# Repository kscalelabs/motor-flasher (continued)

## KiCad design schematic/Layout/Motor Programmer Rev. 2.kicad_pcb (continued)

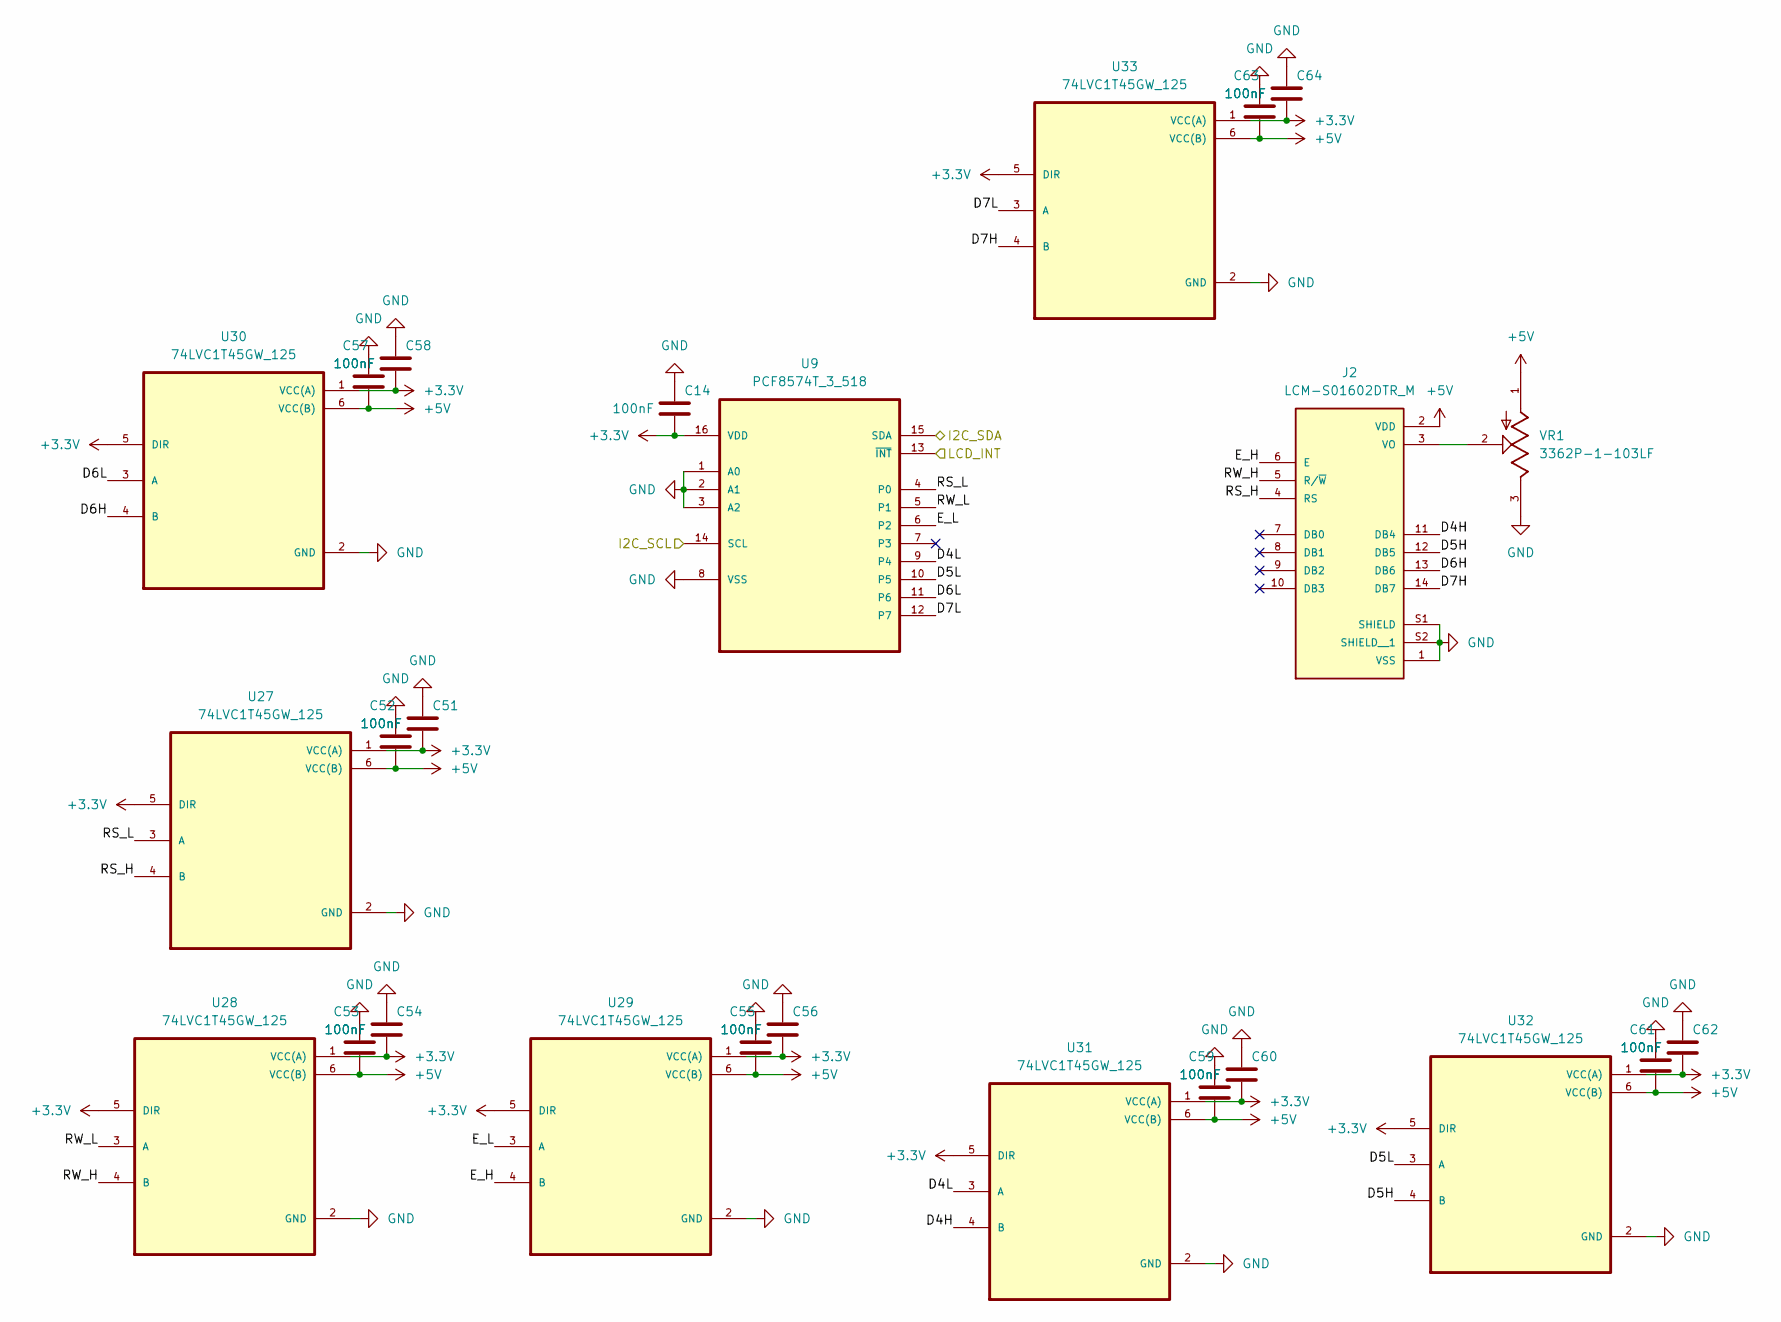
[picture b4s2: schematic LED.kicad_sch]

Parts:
C14, C51, C52, C53, C54, C55, C56, C57, C58, C59, C60, C61, C62, C63, C64: 100nF; C_0402_1005Metric
J2: LCM-S01602DTR_M; LCD_LCM-S01602DTR_M; PARTREV 9/11/02
U9: PCF8574T_3_518; SOIC127P1032X265-16N; MPN PCF8574T/3,518
U27, U28, U29, U30, U31, U32, U33: 74LVC1T45GW_125; SOP65P210X110-6N
VR1: 3362P-1-103LF; TRIM_3362P-1-103LF; PARTREV 08/26/10

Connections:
+3.3V: C14.2, C51.2, C54.2, C56.2, C58.2, C60.2, C62.2, C64.2, U9.16 (VDD), U27.1 (VCC(A)), U27.5 (DIR), U28.1 (VCC(A)), U28.5 (DIR), U29.1 (VCC(A)), U29.5 (DIR), U30.1 (VCC(A)), U30.5 (DIR), U31.1 (VCC(A)), U31.5 (DIR), U32.1 (VCC(A)), U32.5 (DIR), U33.1 (VCC(A)), U33.5 (DIR); also elsewhere on the board
+5V: C52.2, C53.2, C55.2, C57.2, C59.2, C61.2, C63.2, J2.2 (VDD), U27.6 (VCC(B)), U28.6 (VCC(B)), U29.6 (VCC(B)), U30.6 (VCC(B)), U31.6 (VCC(B)), U32.6 (VCC(B)), U33.6 (VCC(B)), VR1.1; also elsewhere on the board
/LCD_Int: U9.13 (~INT); also elsewhere on the board
/LED/D4H: J2.11 (DB4), U31.4 (B)
/LED/D4L: U9.9 (P4), U31.3 (A)
/LED/D5H: J2.12 (DB5), U32.4 (B)
/LED/D5L: U9.10 (P5), U32.3 (A)
/LED/D6H: J2.13 (DB6), U30.4 (B)
/LED/D6L: U9.11 (P6), U30.3 (A)
/LED/D7H: J2.14 (DB7), U33.4 (B)
/LED/D7L: U9.12 (P7), U33.3 (A)
/LED/E_H: J2.6 (E), U29.4 (B)
/LED/E_L: U9.6 (P2), U29.3 (A)
/LED/RS_H: J2.4 (RS), U27.4 (B)
/LED/RS_L: U9.4 (P0), U27.3 (A)
/LED/RW_H: J2.5 (R/~W), U28.4 (B)
/LED/RW_L: U9.5 (P1), U28.3 (A)
/SCL: U9.14 (SCL); also elsewhere on the board
/SDA: U9.15 (SDA); also elsewhere on the board
GND: C14.1, C51.1, C52.1, C53.1, C54.1, C55.1, C56.1, C57.1, C58.1, C59.1, C60.1, C61.1, C62.1, C63.1, C64.1, J2.1 (VSS), J2.S1 (SHIELD), J2.S2 (SHIELD__1), U9.1 (A0), U9.2 (A1), U9.3 (A2), U9.8 (VSS), U27.2 (GND), U28.2 (GND), U29.2 (GND), U30.2 (GND), U31.2 (GND), U32.2 (GND), U33.2 (GND), VR1.3; also elsewhere on the board
unnamed: J2.3 (VO), VR1.2

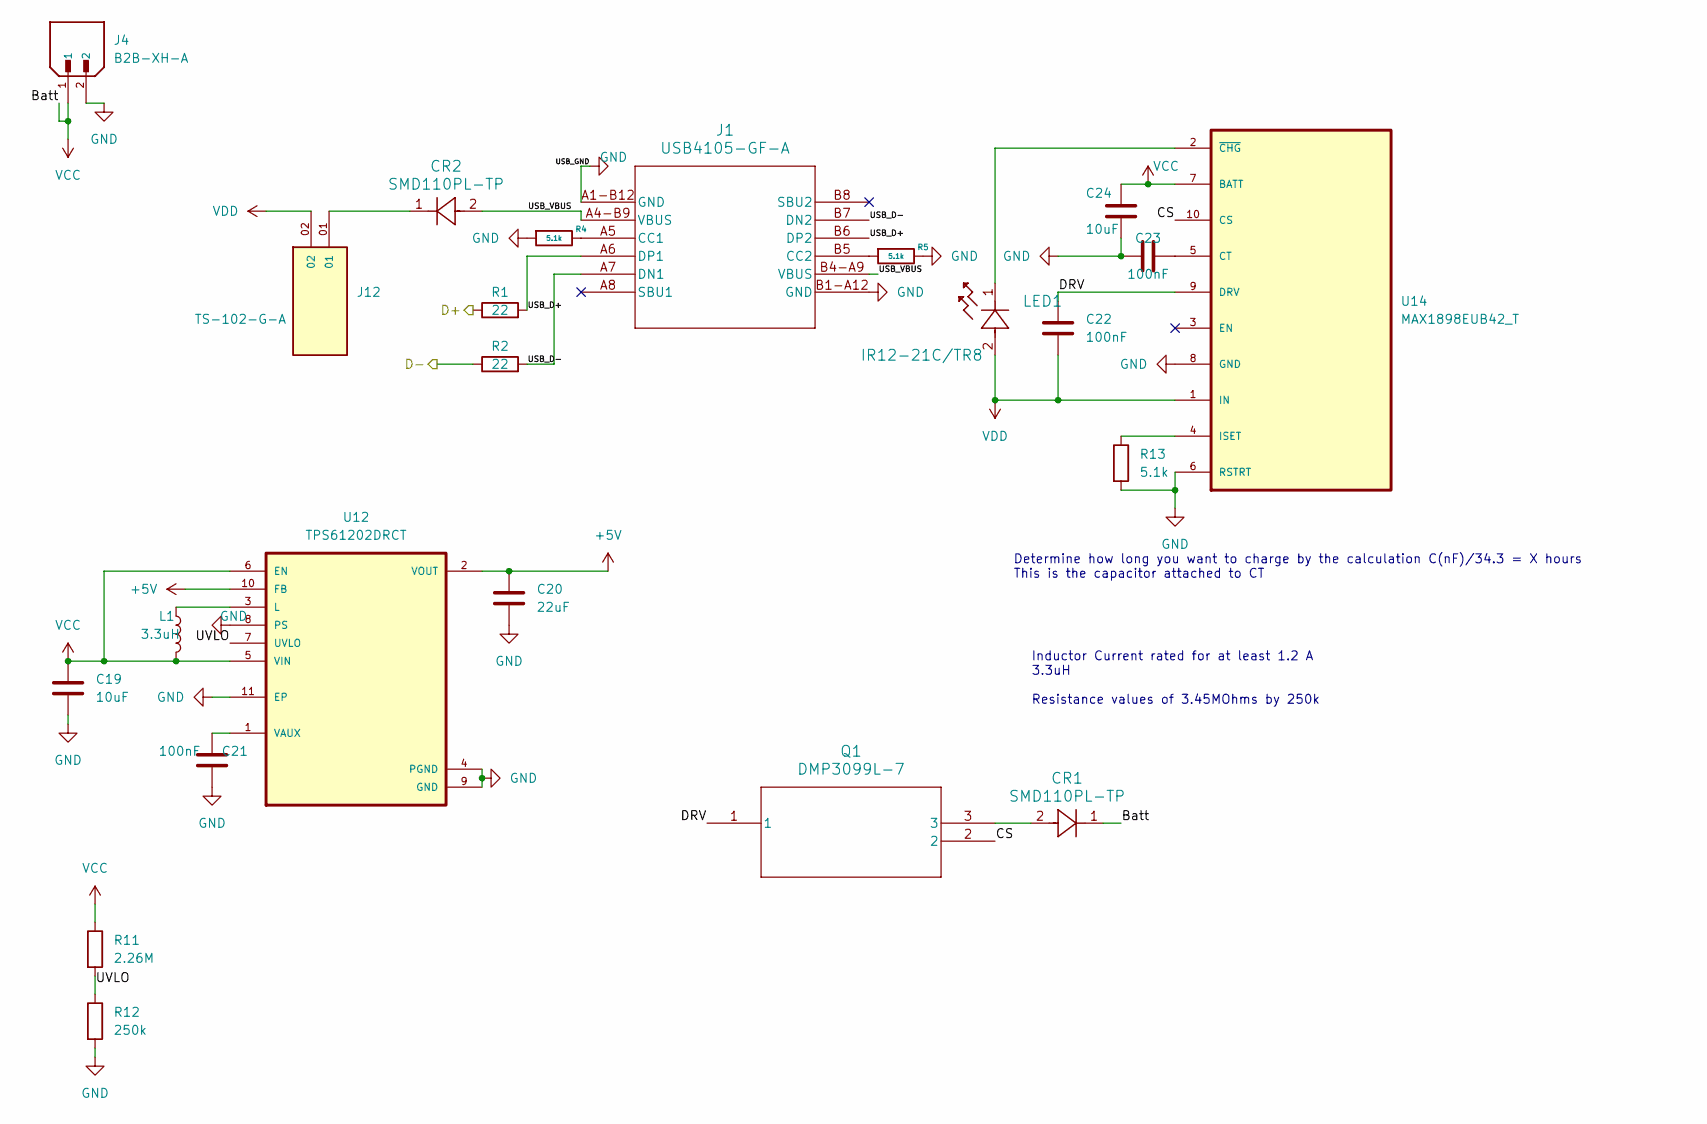
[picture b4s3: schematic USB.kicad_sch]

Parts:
C19, C24: 10uF; C_0805_2012Metric
C20: 22uF; C_0603_1608Metric
C21, C22, C23: 100nF; C_0402_1005Metric
CR1, CR2: SMD110PL-TP; SOD-123FL_MCC
J1: USB4105-GF-A; GCT_USB4105-GF-A
J4: B2B-XH-A; JST_B2B-XH-A; PARTREV N/A
J12: TS-102-G-A; SAMTEC_TS-102-G-A; PARTREV R
L1: 3.3uH; IND_TAIYO_NRS4018_TAY
LED1: IR12-21C/TR8; LED_IR12-21C&slash_TR8_EVE
Q1: DMP3099L-7; DMP3099L-7_DIO
R1, R2: 22; R_0402_1005Metric
R4, R5, R13: 5.1k; R_0603_1608Metric
R11: 2.26M; R_0603_1608Metric
R12: 250k; R_0805_2012Metric
U12: TPS61202DRCT; VREG_V62_16624-01YE
U14: MAX1898EUB42_T; SOP50P490X110-10N

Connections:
+5V: C20.1, U12.2 (VOUT), U12.10 (FB); also elsewhere on the board
/D+: R1.1; also elsewhere on the board
/D-: R2.1; also elsewhere on the board
/USB + Power Source/CS: Q1.2, U14.10 (CS)
/USB + Power Source/DRV: C22.2, Q1.1, U14.9 (DRV)
/USB + Power Source/USB_D+: J1.A6 (DP1), J1.B6 (DP2), R1.2
/USB + Power Source/USB_D-: J1.A7 (DN1), J1.B7 (DN2), R2.2
/USB + Power Source/USB_VBUS: CR2.2, J1.A4-B9 (VBUS), J1.B4-A9 (VBUS)
/USB + Power Source/UVLO: R11.2, R12.1, U12.7 (UVLO)
GND: C19.2, C20.2, C21.2, C23.2, C24.2, J1.A1-B12 (GND), J1.B1-A12 (GND), J4.2, R4.2, R5.1, R12.2, R13.2, U12.4 (PGND), U12.8 (PS), U12.9 (GND), U12.11 (EP), U14.6 (RSTRT), U14.8 (GND); also elsewhere on the board
unnamed: CR1.2, Q1.3
unnamed: CR2.1, J12.01
unnamed: J1.A5 (CC1), R4.1
unnamed: J1.B5 (CC2), R5.2
unnamed: L1.1, U12.3 (L)
unnamed: C21.1, U12.1 (VAUX)
unnamed: C23.1, U14.5 (CT)
unnamed: R13.1, U14.4 (ISET)
unnamed: LED1.1, U14.2 (~CHG)
VCC: C19.1, C24.1, CR1.1, J4.1, L1.2, R11.1, U12.5 (VIN), U12.6 (EN), U14.7 (BATT); also elsewhere on the board
VDD: C22.1, J12.02, LED1.2, U14.1 (IN)

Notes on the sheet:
Inductor Current rated for at least 1.2 A 3.3uH Resistance values of 3.45MOhms by 250k
Determine how long you want to charge by the calculation C(nF)/34.3 = X hours This is the capacitor attached to CT

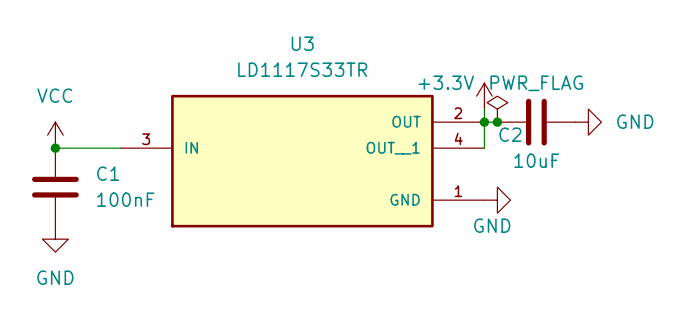
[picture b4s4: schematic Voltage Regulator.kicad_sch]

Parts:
C1: 100nF; C_0402_1005Metric
C2: 10uF; C_0805_2012Metric
U3: LD1117S33TR; SOT230P700X180-4N

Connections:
+3.3V: C2.2, U3.2 (OUT), U3.4 (OUT__1); also elsewhere on the board
GND: C1.2, C2.1, U3.1 (GND); also elsewhere on the board
VCC: C1.1, U3.3 (IN); also elsewhere on the board

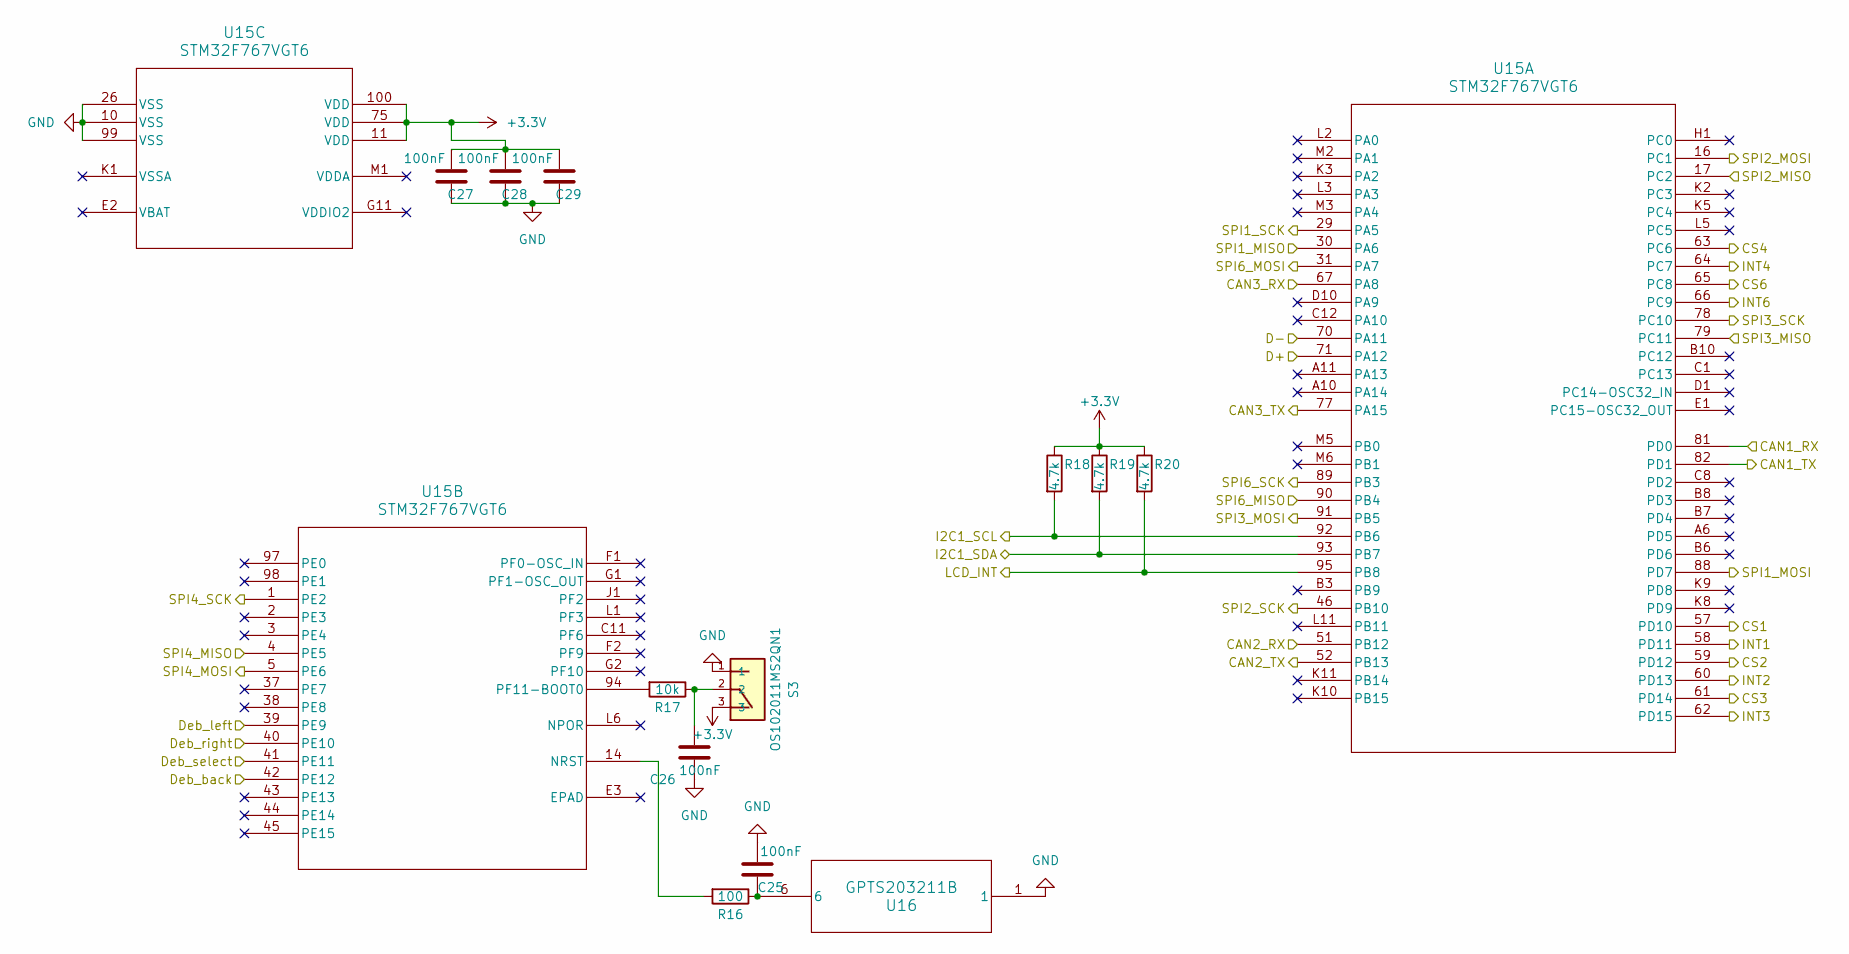
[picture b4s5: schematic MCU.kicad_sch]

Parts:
C25, C26, C27, C28, C29: 100nF; C_0402_1005Metric
R16: 100; R_0402_1005Metric
R17: 10k; R_0402_1005Metric
R18, R19, R20: 4.7k; R_0402_1005Metric
S3: OS102011MS2QN1; SW_OS102011MS2QN1
U15: STM32F767VGT6; QFP50P1600X1600X160-100N
U16: GPTS203211B; SWITCH_03211B

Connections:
+3.3V: C27.1, C28.1, C29.1, R18.1, R19.1, R20.1, S3.3, U15.11 (VDD), U15.75 (VDD), U15.100 (VDD); also elsewhere on the board
/CAN1_RX: U15.81 (PD0); also elsewhere on the board
/CAN1_TX: U15.82 (PD1); also elsewhere on the board
/CAN2_RX: U15.51 (PB12); also elsewhere on the board
/CAN2_TX: U15.52 (PB13); also elsewhere on the board
/CAN3_RX: U15.67 (PA8); also elsewhere on the board
/CAN3_TX: U15.77 (PA15); also elsewhere on the board
/CS1: U15.57 (PD10); also elsewhere on the board
/CS2: U15.59 (PD12); also elsewhere on the board
/CS3: U15.61 (PD14); also elsewhere on the board
/CS4: U15.63 (PC6); also elsewhere on the board
/CS6: U15.65 (PC8); also elsewhere on the board
/D+: U15.71 (PA12); also elsewhere on the board
/D-: U15.70 (PA11); also elsewhere on the board
/Deb_back: U15.42 (PE12); also elsewhere on the board
/Deb_left: U15.39 (PE9); also elsewhere on the board
/Deb_right: U15.40 (PE10); also elsewhere on the board
/Deb_select: U15.41 (PE11); also elsewhere on the board
/INT1: U15.58 (PD11); also elsewhere on the board
/INT2: U15.60 (PD13); also elsewhere on the board
/INT3: U15.62 (PD15); also elsewhere on the board
/INT4: U15.64 (PC7); also elsewhere on the board
/INT6: U15.66 (PC9); also elsewhere on the board
/LCD_Int: R20.2, U15.95 (PB8); also elsewhere on the board
/SCL: R18.2, U15.92 (PB6); also elsewhere on the board
/SDA: R19.2, U15.93 (PB7); also elsewhere on the board
/SPI1_MISO: U15.30 (PA6); also elsewhere on the board
/SPI1_MOSI: U15.88 (PD7); also elsewhere on the board
/SPI1_SCK: U15.29 (PA5); also elsewhere on the board
/SPI2_MISO: U15.17 (PC2); also elsewhere on the board
/SPI2_MOSI: U15.16 (PC1); also elsewhere on the board
/SPI2_SCK: U15.46 (PB10); also elsewhere on the board
/SPI3_MISO: U15.79 (PC11); also elsewhere on the board
/SPI3_MOSI: U15.91 (PB5); also elsewhere on the board
/SPI3_SCK: U15.78 (PC10); also elsewhere on the board
/SPI4_MISO: U15.4 (PE5); also elsewhere on the board
/SPI4_MOSI: U15.5 (PE6); also elsewhere on the board
/SPI4_SCK: U15.1 (PE2); also elsewhere on the board
/SPI6_MISO: U15.90 (PB4); also elsewhere on the board
/SPI6_MOSI: U15.31 (PA7); also elsewhere on the board
/SPI6_SCK: U15.89 (PB3); also elsewhere on the board
GND: C25.2, C26.1, C27.2, C28.2, C29.2, S3.1, U15.10 (VSS), U15.26 (VSS), U15.99 (VSS), U16.1; also elsewhere on the board
unnamed: C25.1, R16.1, U16.6
unnamed: C26.2, R17.1, S3.2
unnamed: R16.2, U15.14 (NRST)
unnamed: R17.2, U15.94 (PF11-BOOT0)

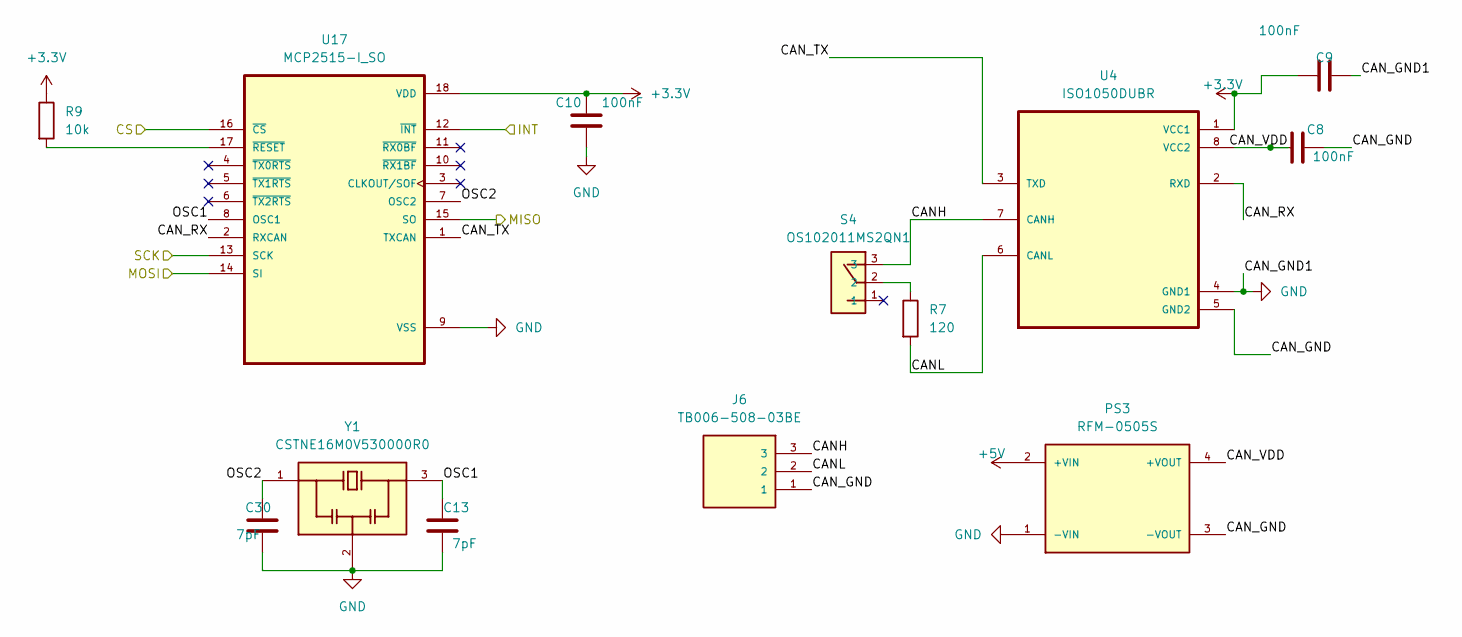
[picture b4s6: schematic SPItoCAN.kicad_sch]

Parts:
C8, C9, C10: 100nF; C_0402_1005Metric
C13, C30: 7pF; C_0603_1608Metric
J6: TB006-508-03BE; CUI_TB006-508-03BE
PS3: RFM-0505S; CONV_RFM-0505S; PARTREV 0
R7: 120; R_0402_1005Metric
R9: 10k; R_0402_1005Metric
S4: OS102011MS2QN1; SW_OS102011MS2QN1
U4: ISO1050DUBR; SOP254P1040X485-8N
U17: MCP2515-I_SO; SOIC127P1030X265-18N
Y1: CSTNE16M0V530000R0; OSC_CSTNE16M0V530000R0; PARTREV JGC42-8853B

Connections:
+3.3V: C9.1, C10.2, R9.1, U4.1 (VCC1), U17.18 (VDD); also elsewhere on the board
+5V: PS3.2 (+VIN); also elsewhere on the board
/CAN4/CANH: J6.3, S4.3, U4.7 (CANH)
/CAN4/CANL: J6.2, R7.2, U4.6 (CANL)
/CAN4/CAN_GND: C8.2, J6.1, PS3.3 (-VOUT), U4.5 (GND2)
/CAN4/CAN_RX: U4.2 (RXD), U17.2 (RXCAN)
/CAN4/CAN_TX: U4.3 (TXD), U17.1 (TXCAN)
/CAN4/CAN_VDD: C8.1, PS3.4 (+VOUT), U4.8 (VCC2)
/CAN4/OSC1: C13.1, U17.8 (OSC1), Y1.3
/CAN4/OSC2: C30.1, U17.7 (OSC2), Y1.1
/CS1: U17.16 (~CS); also elsewhere on the board
/INT1: U17.12 (~INT); also elsewhere on the board
/SPI1_MISO: U17.15 (SO); also elsewhere on the board
/SPI1_MOSI: U17.14 (SI); also elsewhere on the board
/SPI1_SCK: U17.13 (SCK); also elsewhere on the board
GND: C9.2, C10.1, C13.2, C30.2, PS3.1 (-VIN), U4.4 (GND1), U17.9 (VSS), Y1.2; also elsewhere on the board
unnamed: R7.1, S4.2
unnamed: R9.2, U17.17 (~RESET)

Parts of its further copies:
C31, C32, C36, C37, C41, C42, C46, C47: 7pF; C_0603_1608Metric
C33, C34, C35, C38, C39, C40, C43, C44, C45, C48, C49, C50: 100nF; C_0402_1005Metric
J8, J9, J10, J11: TB006-508-03BE; CUI_TB006-508-03BE
PS5, PS6, PS7, PS8: RFM-0505S; CONV_RFM-0505S; PARTREV 0
R10, R22, R24, R26: 10k; R_0402_1005Metric
R21, R23, R25, R27: 120; R_0402_1005Metric
S6, S7, S8, S9: OS102011MS2QN1; SW_OS102011MS2QN1
U19, U21, U23, U25: MCP2515-I_SO; SOIC127P1030X265-18N
U20, U22, U24, U26: ISO1050DUBR; SOP254P1040X485-8N
Y2, Y3, Y4, Y5: CSTNE16M0V530000R0; OSC_CSTNE16M0V530000R0; PARTREV JGC42-8853B

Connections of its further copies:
+3.3V: C33.2, C35.1, C38.2, C40.1, C43.2, C45.1, C48.2, C50.1, R10.1, R22.1, R24.1, R26.1, U19.18 (VDD), U20.1 (VCC1), U21.18 (VDD), U22.1 (VCC1), U23.18 (VDD), U24.1 (VCC1), U25.18 (VDD), U26.1 (VCC1); also elsewhere on the board
+5V: PS5.2 (+VIN), PS6.2 (+VIN), PS7.2 (+VIN), PS8.2 (+VIN); also elsewhere on the board
/CAN5/CANH: J8.3, S6.3, U20.7 (CANH)
/CAN5/CANL: J8.2, R21.2, U20.6 (CANL)
/CAN5/CAN_GND: C34.2, J8.1, PS5.3 (-VOUT), U20.5 (GND2)
/CAN5/CAN_RX: U19.2 (RXCAN), U20.2 (RXD)
/CAN5/CAN_TX: U19.1 (TXCAN), U20.3 (TXD)
/CAN5/CAN_VDD: C34.1, PS5.4 (+VOUT), U20.8 (VCC2)
/CAN5/OSC1: C32.1, U19.8 (OSC1), Y2.3
/CAN5/OSC2: C31.1, U19.7 (OSC2), Y2.1
/CAN6/CANH: J9.3, S7.3, U22.7 (CANH)
/CAN6/CANL: J9.2, R23.2, U22.6 (CANL)
/CAN6/CAN_GND: C39.2, J9.1, PS6.3 (-VOUT), U22.5 (GND2)
/CAN6/CAN_RX: U21.2 (RXCAN), U22.2 (RXD)
/CAN6/CAN_TX: U21.1 (TXCAN), U22.3 (TXD)
/CAN6/CAN_VDD: C39.1, PS6.4 (+VOUT), U22.8 (VCC2)
/CAN6/OSC1: C37.1, U21.8 (OSC1), Y3.3
/CAN6/OSC2: C36.1, U21.7 (OSC2), Y3.1
/CAN7/CANH: J10.3, S8.3, U24.7 (CANH)
/CAN7/CANL: J10.2, R25.2, U24.6 (CANL)
/CAN7/CAN_GND: C44.2, J10.1, PS7.3 (-VOUT), U24.5 (GND2)
/CAN7/CAN_RX: U23.2 (RXCAN), U24.2 (RXD)
/CAN7/CAN_TX: U23.1 (TXCAN), U24.3 (TXD)
/CAN7/CAN_VDD: C44.1, PS7.4 (+VOUT), U24.8 (VCC2)
/CAN7/OSC1: C42.1, U23.8 (OSC1), Y4.3
/CAN7/OSC2: C41.1, U23.7 (OSC2), Y4.1
/CAN8/CANH: J11.3, S9.3, U26.7 (CANH)
/CAN8/CANL: J11.2, R27.2, U26.6 (CANL)
/CAN8/CAN_GND: C49.2, J11.1, PS8.3 (-VOUT), U26.5 (GND2)
/CAN8/CAN_RX: U25.2 (RXCAN), U26.2 (RXD)
/CAN8/CAN_TX: U25.1 (TXCAN), U26.3 (TXD)
/CAN8/CAN_VDD: C49.1, PS8.4 (+VOUT), U26.8 (VCC2)
/CAN8/OSC1: C47.1, U25.8 (OSC1), Y5.3
/CAN8/OSC2: C46.1, U25.7 (OSC2), Y5.1
/CS2: U19.16 (~CS); also elsewhere on the board
/CS3: U21.16 (~CS); also elsewhere on the board
/CS4: U23.16 (~CS); also elsewhere on the board
/CS6: U25.16 (~CS); also elsewhere on the board
/INT2: U19.12 (~INT); also elsewhere on the board
/INT3: U21.12 (~INT); also elsewhere on the board
/INT4: U23.12 (~INT); also elsewhere on the board
/INT6: U25.12 (~INT); also elsewhere on the board
/SPI2_MISO: U19.15 (SO); also elsewhere on the board
/SPI2_MOSI: U19.14 (SI); also elsewhere on the board
/SPI2_SCK: U19.13 (SCK); also elsewhere on the board
/SPI3_MISO: U21.15 (SO); also elsewhere on the board
/SPI3_MOSI: U21.14 (SI); also elsewhere on the board
/SPI3_SCK: U21.13 (SCK); also elsewhere on the board
/SPI4_MISO: U23.15 (SO); also elsewhere on the board
/SPI4_MOSI: U23.14 (SI); also elsewhere on the board
/SPI4_SCK: U23.13 (SCK); also elsewhere on the board
/SPI6_MISO: U25.15 (SO); also elsewhere on the board
/SPI6_MOSI: U25.14 (SI); also elsewhere on the board
/SPI6_SCK: U25.13 (SCK); also elsewhere on the board
GND: C31.2, C32.2, C33.1, C35.2, C36.2, C37.2, C38.1, C40.2, C41.2, C42.2, C43.1, C45.2, C46.2, C47.2, C48.1, C50.2, PS5.1 (-VIN), PS6.1 (-VIN), PS7.1 (-VIN), PS8.1 (-VIN), U19.9 (VSS), U20.4 (GND1), U21.9 (VSS), U22.4 (GND1), U23.9 (VSS), U24.4 (GND1), U25.9 (VSS), U26.4 (GND1), Y2.2, Y3.2, Y4.2, Y5.2; also elsewhere on the board
unnamed: R21.1, S6.2
unnamed: R23.1, S7.2
unnamed: R25.1, S8.2
unnamed: R27.1, S9.2
unnamed: R10.2, U19.17 (~RESET)
unnamed: R22.2, U21.17 (~RESET)
unnamed: R24.2, U23.17 (~RESET)
unnamed: R26.2, U25.17 (~RESET)

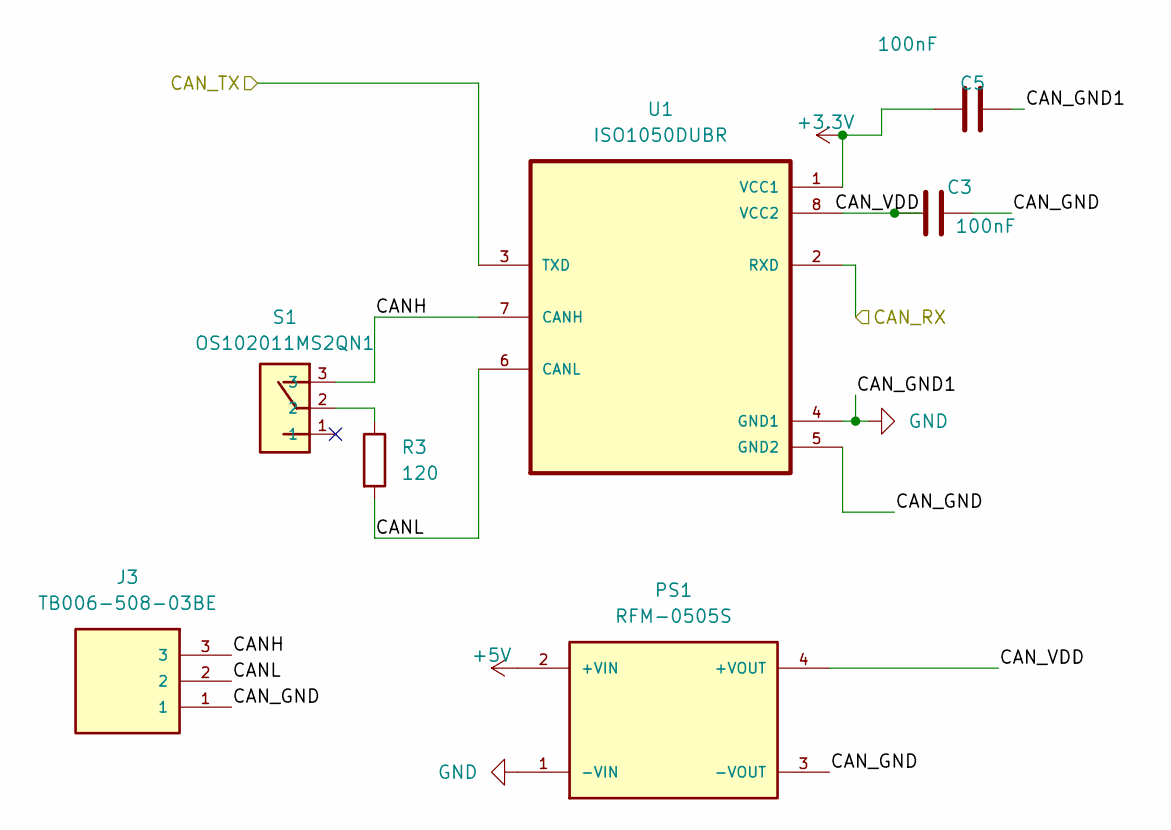
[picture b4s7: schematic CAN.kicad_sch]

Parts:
C3, C5: 100nF; C_0402_1005Metric
J3: TB006-508-03BE; CUI_TB006-508-03BE
PS1: RFM-0505S; CONV_RFM-0505S; PARTREV 0
R3: 120; R_0402_1005Metric
S1: OS102011MS2QN1; SW_OS102011MS2QN1
U1: ISO1050DUBR; SOP254P1040X485-8N

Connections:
+3.3V: C5.1, U1.1 (VCC1); also elsewhere on the board
+5V: PS1.2 (+VIN); also elsewhere on the board
/CAN1/CANH: J3.3, S1.3, U1.7 (CANH)
/CAN1/CANL: J3.2, R3.2, U1.6 (CANL)
/CAN1/CAN_GND: C3.2, J3.1, PS1.3 (-VOUT), U1.5 (GND2)
/CAN1/CAN_VDD: C3.1, PS1.4 (+VOUT), U1.8 (VCC2)
/CAN1_RX: U1.2 (RXD); also elsewhere on the board
/CAN1_TX: U1.3 (TXD); also elsewhere on the board
GND: C5.2, PS1.1 (-VIN), U1.4 (GND1); also elsewhere on the board
unnamed: R3.1, S1.2

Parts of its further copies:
C6, C7, C11, C12: 100nF; C_0402_1005Metric
J5, J7: TB006-508-03BE; CUI_TB006-508-03BE
PS2, PS4: RFM-0505S; CONV_RFM-0505S; PARTREV 0
R6, R8: 120; R_0402_1005Metric
S2, S5: OS102011MS2QN1; SW_OS102011MS2QN1
U2, U18: ISO1050DUBR; SOP254P1040X485-8N

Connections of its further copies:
+3.3V: C7.1, C12.1, U2.1 (VCC1), U18.1 (VCC1); also elsewhere on the board
+5V: PS2.2 (+VIN), PS4.2 (+VIN); also elsewhere on the board
/CAN2/CANH: J5.3, S2.3, U2.7 (CANH)
/CAN2/CANL: J5.2, R6.2, U2.6 (CANL)
/CAN2/CAN_GND: C6.2, J5.1, PS2.3 (-VOUT), U2.5 (GND2)
/CAN2/CAN_VDD: C6.1, PS2.4 (+VOUT), U2.8 (VCC2)
/CAN2_RX: U2.2 (RXD); also elsewhere on the board
/CAN2_TX: U2.3 (TXD); also elsewhere on the board
/CAN3/CANH: J7.3, S5.3, U18.7 (CANH)
/CAN3/CANL: J7.2, R8.2, U18.6 (CANL)
/CAN3/CAN_GND: C11.2, J7.1, PS4.3 (-VOUT), U18.5 (GND2)
/CAN3/CAN_VDD: C11.1, PS4.4 (+VOUT), U18.8 (VCC2)
/CAN3_RX: U18.2 (RXD); also elsewhere on the board
/CAN3_TX: U18.3 (TXD); also elsewhere on the board
GND: C7.2, C12.2, PS2.1 (-VIN), PS4.1 (-VIN), U2.4 (GND1), U18.4 (GND1); also elsewhere on the board
unnamed: R6.1, S2.2
unnamed: R8.1, S5.2

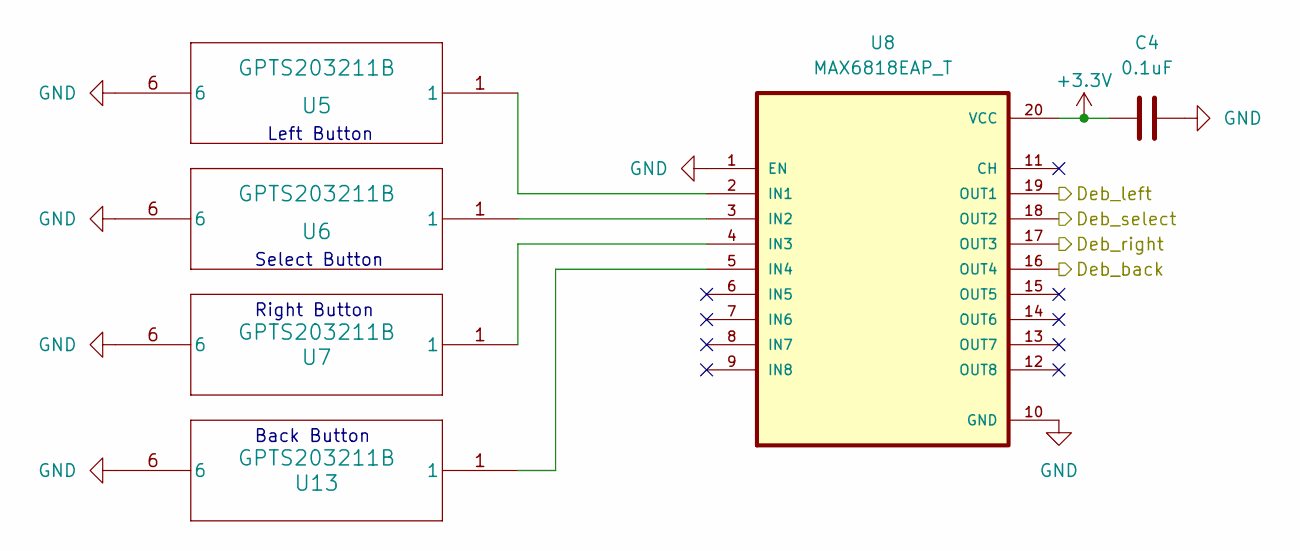
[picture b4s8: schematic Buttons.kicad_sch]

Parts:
C4: 0.1uF; C_0402_1005Metric
U5, U6, U7, U13: GPTS203211B; SWITCH_03211B
U8: MAX6818EAP_T; SOP65P777X199-20N

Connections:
+3.3V: C4.1, U8.20 (VCC); also elsewhere on the board
/Deb_back: U8.16 (OUT4); also elsewhere on the board
/Deb_left: U8.19 (OUT1); also elsewhere on the board
/Deb_right: U8.17 (OUT3); also elsewhere on the board
/Deb_select: U8.18 (OUT2); also elsewhere on the board
GND: C4.2, U5.6, U6.6, U7.6, U8.1 (EN), U8.10 (GND), U13.6; also elsewhere on the board
unnamed: U5.1, U8.2 (IN1)
unnamed: U6.1, U8.3 (IN2)
unnamed: U7.1, U8.4 (IN3)
unnamed: U8.5 (IN4), U13.1

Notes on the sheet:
Back Button
Left Button
Select Button
Right Button

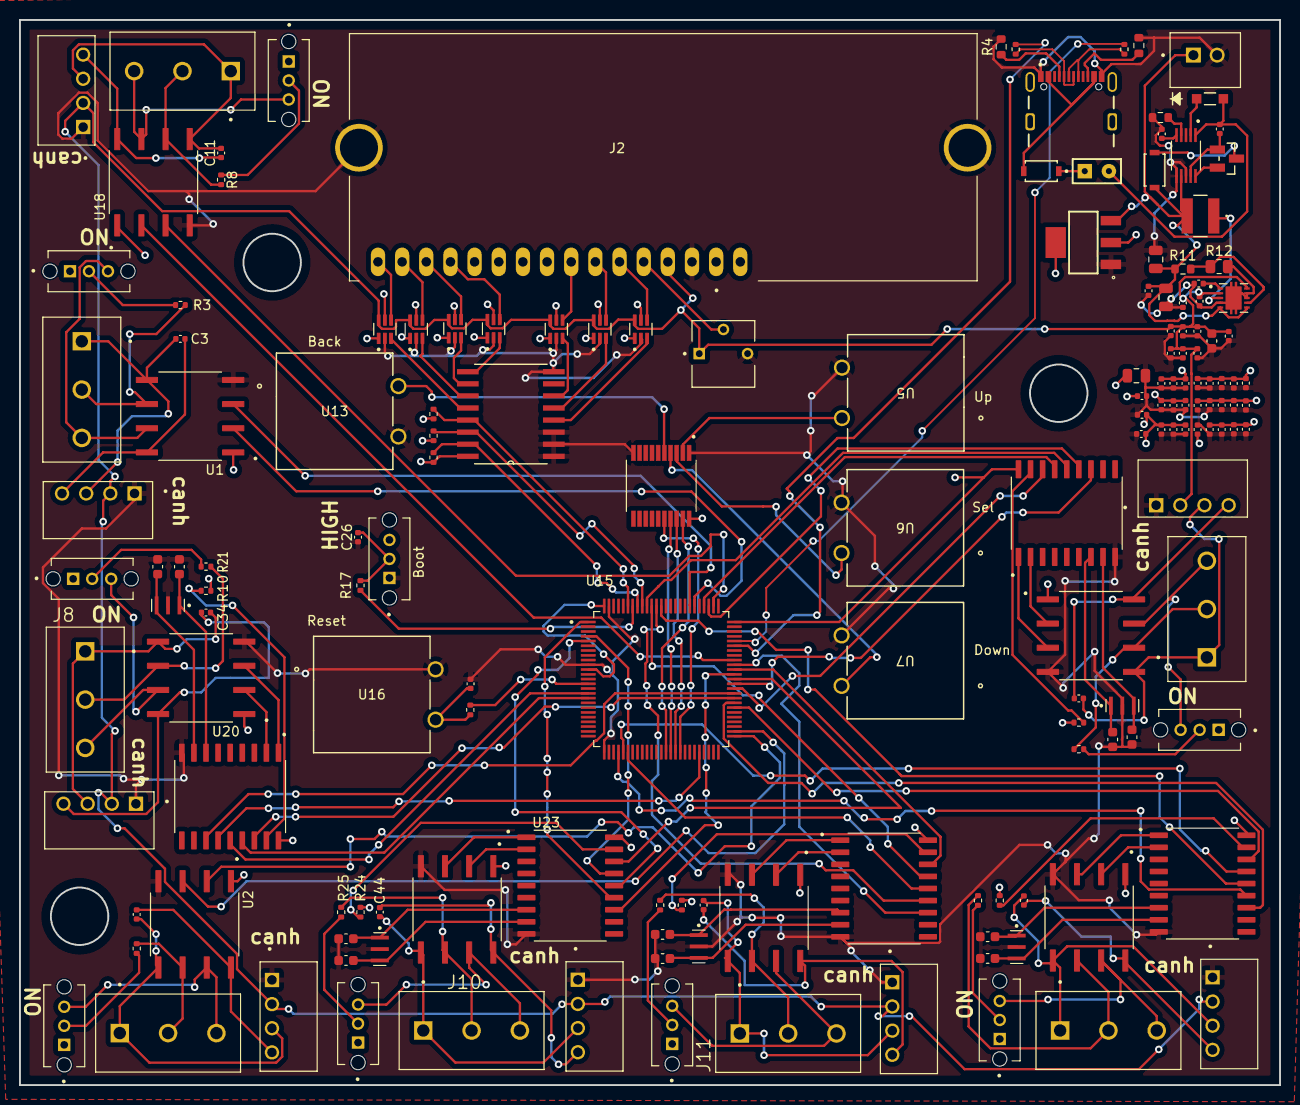
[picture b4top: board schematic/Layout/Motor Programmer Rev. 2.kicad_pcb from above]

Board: 2 copper layers, 132.5 x 112.0 mm, 160 parts (0 on the bottom side), 148 nets.

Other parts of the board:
C15, C16, C17, C18: 100nF; C_0402_1005Metric

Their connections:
+3.3V: C16.2, C18.2; also elsewhere on the board
+5V: C15.2, C17.2; also elsewhere on the board
GND: C15.1, C16.1, C17.1, C18.1; also elsewhere on the board

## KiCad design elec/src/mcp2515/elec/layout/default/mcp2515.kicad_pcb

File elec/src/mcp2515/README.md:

# mcp2515

Wooohooo a new package!

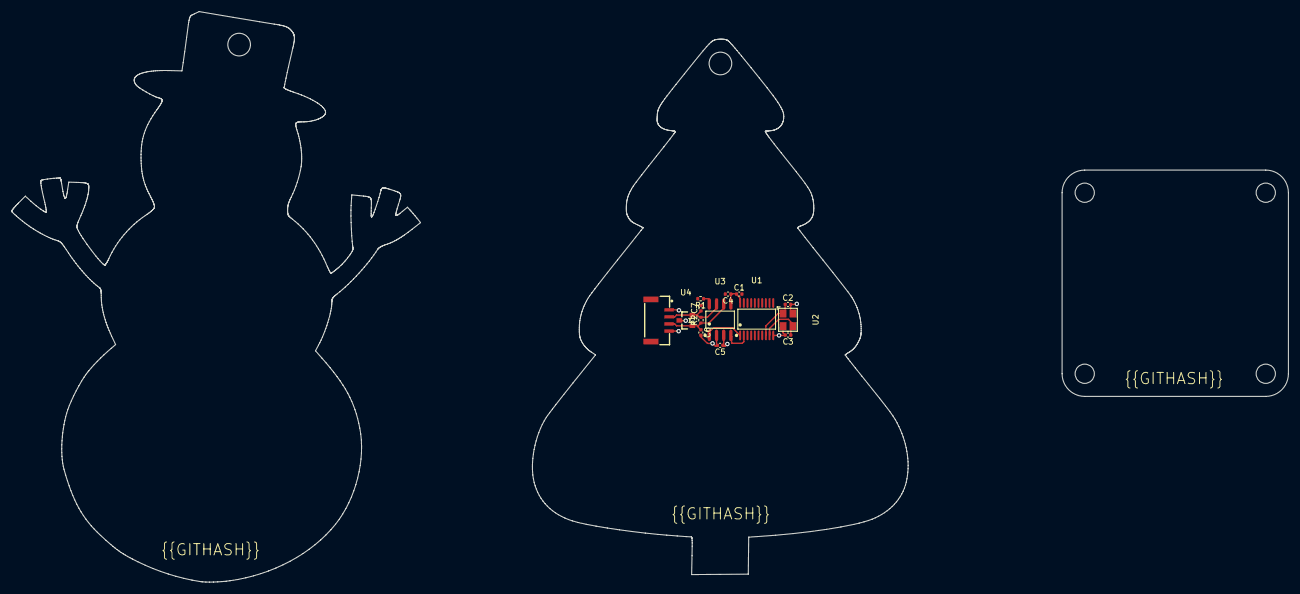
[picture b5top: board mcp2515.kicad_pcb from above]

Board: 2 copper layers, 66.4 x 94.6 mm, 14 parts (0 on the bottom side), 10 nets.

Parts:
C1, C4, C5: 16V 100nF X7R ±10% 0402 Multilayer Ceramic Capaci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; C0402
C2, C3: 50V 8.2pF C0G 0402 Multilayer Ceramic Capacitors 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; C0402
C6, C7: 50V 47nF X7R ±10% 0402 Multilayer Ceramic Capacit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; C0402
J1: CONN-SMD_4P-P1.25_SM04B-GHS-TB-LF-SN
R1: 62.5mW Thick Film Resistors 50V ±100ppm/℃ ±1% 10k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; R0402
R2: 62.5mW Thick Film Resistors 50V ±100ppm/℃ ±1% 120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; R0402
U1: TSSOP-20_L6.5-W4.4-P0.65-LS6.4-BL
U2: OSC-SMD_4P-L3.2-W2.5-BL
U3: SOIC-8_L4.9-W3.9-P1.27-LS6.0-BL
U4: SOT-23_L2.9-W1.3-P1.90-LS2.4-BR

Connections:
canh: C7.1, J1.2, R2.2, U3.7, U4.2
canl: C6.1, J1.3, R2.1, U3.6, U4.1
controller-vcc: C2.1, U1.8, U2.1
controller-vcc-1: C3.1, U1.9, U2.3
gnd-1: C1.2, C2.2, C3.2, C4.2, C5.2, C6.2, C7.2, J1.4, R1.2, U1.10, U2.2, U2.4, U3.2, U4.3
rx: U1.2, U3.4
transceiver-vcc: R1.1, U3.8
tx: U1.1, U3.1
vcc: C1.1, C4.1, U1.20, U3.5
vcc-1: C5.1, J1.1, U3.3

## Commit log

2024-06-22 Adding Revisions 2 and 3
2024-06-26 CAN-Daddy-Release
2024-06-26 Revision 2 Added
2024-06-26 Cleaned up Master
2024-06-26 Placed into singular folder
2024-06-26 Changed name of Kicad File
2024-07-07 Pushing current changes
2024-07-07 Added Updates
2024-07-07 Changed to Kicad Version 8
2024-07-09 Starting layout
2024-07-12 Beginning Layout Process
2024-07-12 Removed ERC Errors and Warnings
2024-07-13 Rough Placement and Design
2024-07-27 Saving current revision
2024-07-27 Beginning Work on Infineon Controller
2024-08-06 Current Changes pushed
